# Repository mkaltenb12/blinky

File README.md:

# Blinky HTL-Steyr

Astabile Kippstufe mit 2 NPN-Transistoren für eine 9V-Blockbatterie.

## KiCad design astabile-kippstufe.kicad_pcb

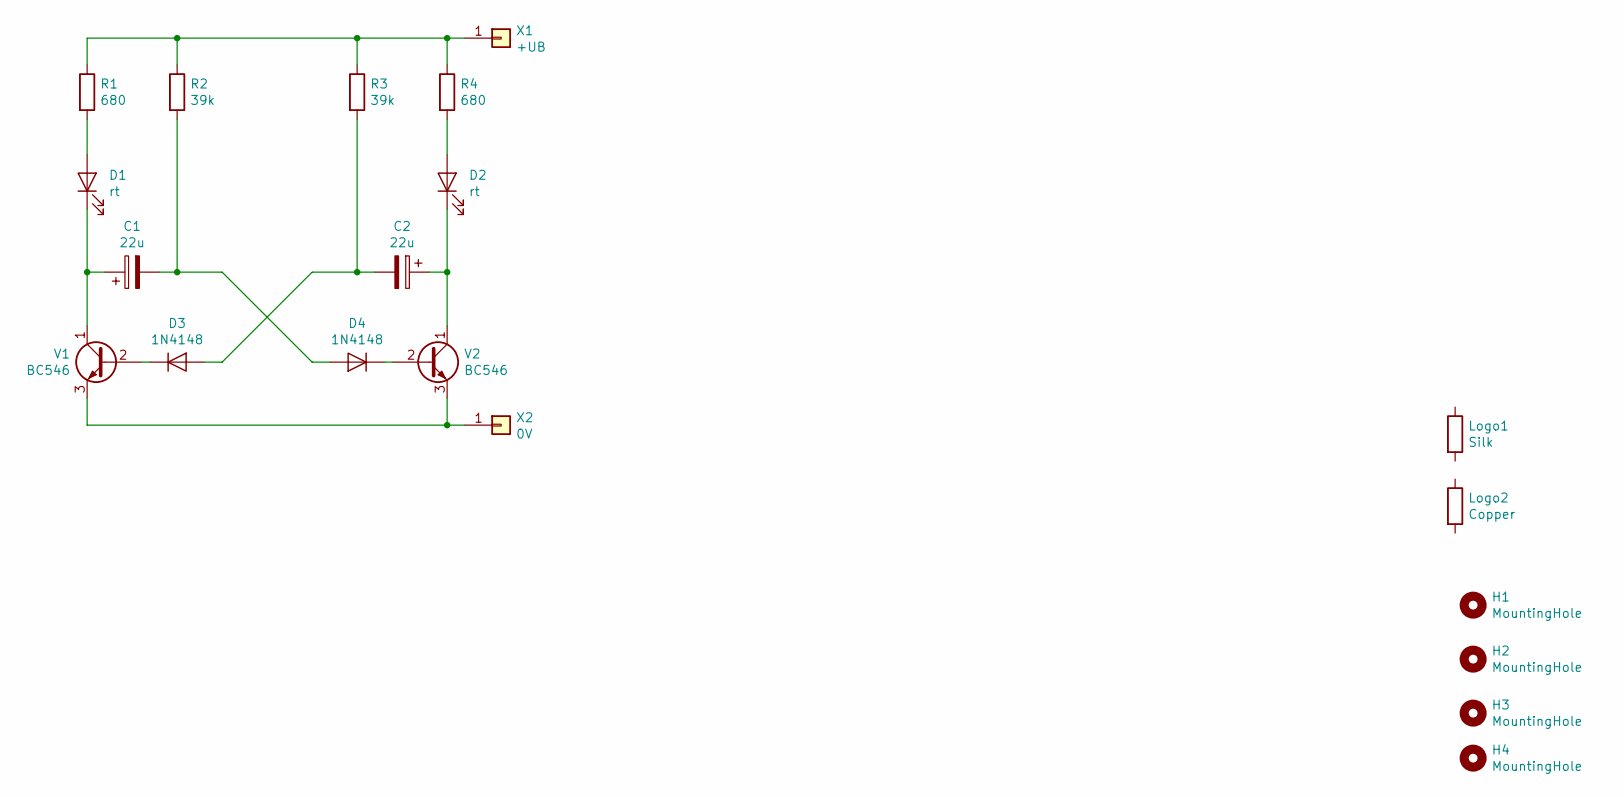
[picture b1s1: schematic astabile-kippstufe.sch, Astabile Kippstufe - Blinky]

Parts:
C1, C2: 22u; CP_Radial_D10.0mm_P5.00mm_P2.50mm
D1, D2: rt; LED_D5.0mm
D3, D4: 1N4148; D_A-405_P7.62mm_Horizontal
H1, H2, H3, H4: MountingHole; MountingHole_3.2mm_M3
Logo1: Silk; HTL-Steyr-Logo_4x4mm_SilkScreen
Logo2: Copper; HTL-Steyr-Logo_4x4mm_Copper
R1, R4: 680; R_Axial_DIN0207_L6.3mm_D2.5mm_P10.16mm_Horizontal
R2, R3: 39k; R_Axial_DIN0207_L6.3mm_D2.5mm_P10.16mm_Horizontal
V1, V2: BC546; TO-92L_HandSolder
X1: +UB; SolderWirePad_3mm_Drill-1mm
X2: 0V; SolderWirePad_3mm_Drill-1mm

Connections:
unnamed: C1.1, D1.1 (K), V1.1 (C)
unnamed: C1.2, D4.2 (A), R2.2
unnamed: C2.1, D2.1 (K), V2.1 (C)
unnamed: C2.2, D3.2 (A), R3.2
unnamed: D1.2 (A), R1.2
unnamed: D2.2 (A), R4.2
unnamed: D3.1 (K), V1.2 (B)
unnamed: D4.1 (K), V2.2 (B)
unnamed: R1.1, R2.1, R3.1, R4.1, X1.1
unnamed: V1.3 (E), V2.3 (E), X2.1

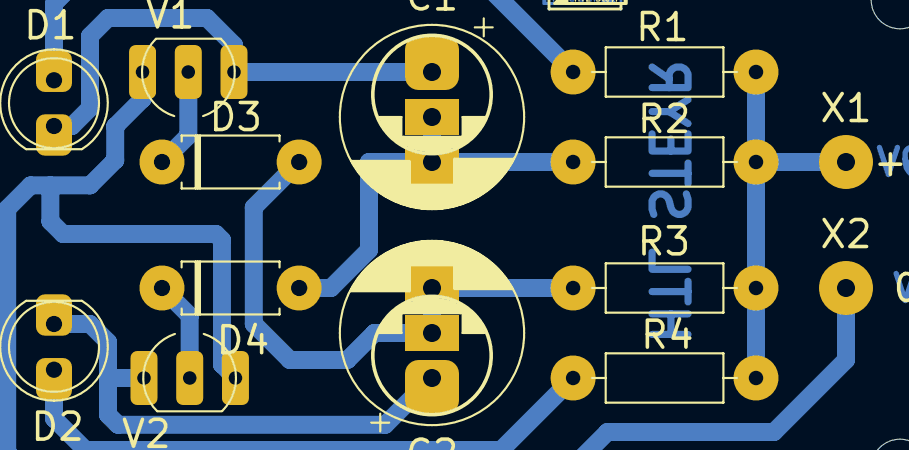
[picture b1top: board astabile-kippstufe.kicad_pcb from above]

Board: 2 copper layers, 20 parts (1 on the bottom side), 10 nets.

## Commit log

2019-12-03 erste version zum probefräsen
2019-12-16 kleinere Anpassungen im Doc, nun Faltbarer Ausdruck
2020-01-17 Änderungen vom 16. Dez. 2019
2020-06-19 v19.0.2 inkl doku und gerber
2020-06-19 post commit, updated PDF
2020-06-22 Add Gitignore for *bak-files
2020-06-22 Add readme for Github
2020-06-22 Montagelöcher
